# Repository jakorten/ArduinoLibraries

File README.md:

# ArduinoLibraries

This repo contains useful Arduino libraries for student and/or research projects.
| Code            | Description                                                                                                |   |
|-----------------|------------------------------------------------------------------------------------------------------------|---|
| [LEDTest](https://github.com/jakorten/SoftRoboticsDevBoard/tree/main/LEDTest)         | Sketch to test the normal LEDs of the DevBoard.                                                            |   |
| [Dual NeoPixel Test](https://github.com/jakorten/SoftRoboticsDevBoard/tree/main/NeoPixelTest) | Simple NeoPixel test for the two Neopixels. |   |
| [ActuatorTest](https://github.com/jakorten/SoftRoboticsDevBoard/tree/main/ActuatorTest)    | Sketch to test the four Actuators of the DevBoard.                                                         |   |
| [WireScanner](https://github.com/jakorten/SoftRoboticsDevBoard/tree/main/WireScanner)     | Sketch that allows to scan all i2c devices on different SERCOM wires of the DevBoard.                                                |   |
| [FRAM_MB85RC_I2C](https://github.com/jakorten/ArduinoLibraries/tree/main/FRAM_MB85RC_I2C) | Is a modified library based on the one from [@sosandroid](https://github.com/sosandroid/FRAM_MB85RC_I2C) that supports SERCOM for Arduino SAMD controllers. |   |

Disclaimer: the sketches and/or libraries might not have been written by myself (but of course I credit the original authors). Coding standards might not be up to the standard we teach and want you to follow. We will try to refactor these libraries as much as possible but often as we need them for rapid prototyping only that might not have been feasible.

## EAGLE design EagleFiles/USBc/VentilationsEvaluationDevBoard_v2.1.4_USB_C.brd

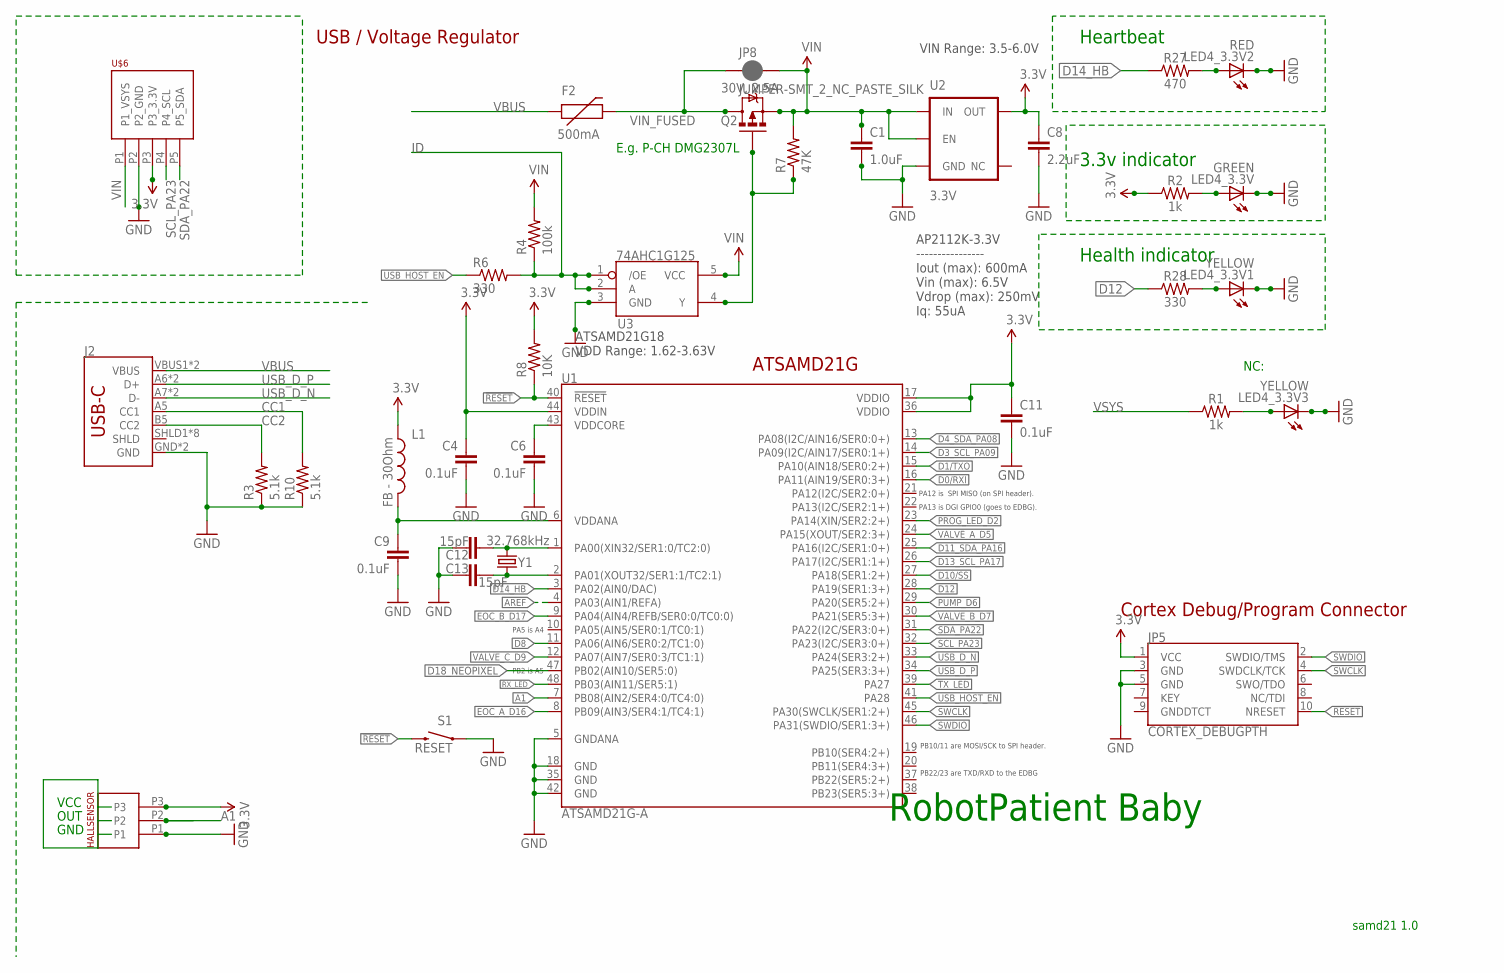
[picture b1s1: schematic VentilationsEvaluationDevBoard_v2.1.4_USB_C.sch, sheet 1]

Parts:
C1: 1.0uF; 0805
C4, C6, C9, C11: 0.1uF; 0402-CAP
C8: 2.2uF; 0603-CAP
C12, C13: 15pF; 0402-CAP
F2: 500mA; PTC-1206
HALLSENSOR: PHOENIX_PTSM_M3_TH_UP; PTSM_M3_THR_UP
J2: USB_C16PIN; USB-C-16P
JP5: CORTEX_DEBUGPTH; 2X5-PTH-1.27MM
JP8: JUMPER-SMT_2_NC_PASTE_SILK; SMT-JUMPER_2_NC_PASTE_SILK
L1: FB - 30Ohm; 0603
LED4_3.3V: GREEN; LED-0603
LED4_3.3V1, LED4_3.3V3: YELLOW; LED-0603
LED4_3.3V2: RED; LED-0603
Q2: 30V, 2.5A; SOT23-3
R1, R2: 1k; 0603
R3, R10: 5.1k; 0603-RES
R4: 100k; 0603-RES
R6: 330; 0603-RES
R7: 47K; 0603-RES
R8: 10K; 0603-RES
R27: 470; 0603
R28: 330; 0603
S1: RESET; TACTILE_SWITCH_SMD_4.6X2.8MM
U1: ATSAMD21G-A; TQFP-48
U2: 3.3V; SOT23-5
U3: 74AHC1G125; SOT23-5
U$6: PHOENIX_PTSM_M5_TH_UP; PTSM_M5_THR_UP
Y1: 32.768kHz; CRYSTAL-SMD-3.2X1.5MM

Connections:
3.3V: C4.1, C8.1, C11.1, HALLSENSOR.P3, JP5.1 (VCC), L1.1, R2.1, R8.2, U1.17 (VDDIO), U1.36 (VDDIO), U1.44 (VDDIN), U2.5 (OUT), U$6.P3 (P3_3.3V); also elsewhere on the board
!RESET: JP5.10 (NRESET), R8.1, S1.3 (2), S1.4 (2), U1.40 (!RESET!)
A1: HALLSENSOR.P2, U1.7 (PB08(AIN2/SER4:0/TC4:0))
AREF: U1.4 (PA03(AIN1/REFA))
CC1: J2.A5 (CC1), R10.2
CC2: J2.B5 (CC2), R3.2
D0/RXI: U1.16 (PA11(AIN19/SER0:3+))
D1/TXO: U1.15 (PA10(AIN18/SER0:2+))
D3_SCL_PA09: U1.14 (PA09(I2C/AIN17/SER0:1+)); also elsewhere on the board
D4_SDA_PA08: U1.13 (PA08(I2C/AIN16/SER0:0+)); also elsewhere on the board
D8: U1.11 (PA06(AIN6/SER0:2/TC1:0))
D10/SS: U1.27 (PA18(SER1:2+))
D11_SDA_PA16: U1.25 (PA16(I2C/SER1:0+)); also elsewhere on the board
D12: R28.1, U1.28 (PA19(SER1:3+))
D13_SCL_PA17: U1.26 (PA17(I2C/SER1:1+)); also elsewhere on the board
D14_HB: R27.1, U1.3 (PA02(AIN0/DAC))
D18_NEOPIXEL: U1.47 (PB02(AIN10/SER5:0)); also elsewhere on the board
EOC_A_D16: U1.8 (PB09(AIN3/SER4:1/TC4:1)); also elsewhere on the board
EOC_B_D17: U1.9 (PA04(AIN4/REFB/SER0:0/TC0:0)); also elsewhere on the board
GND: C1.2, C4.2, C6.2, C8.2, C9.2, C11.2, C12.1, C13.2, HALLSENSOR.P1, J2.GND, J2.GND2 (GND), JP5.3 (GND), JP5.5 (GND), LED4_3.3V.C, LED4_3.3V1.C, LED4_3.3V2.C, LED4_3.3V3.C, R3.1, R10.1, S1.1, S1.2 (1), U1.5 (GNDANA), U1.18 (GND), U1.35 (GND), U1.42 (GND), U2.2 (GND), U3.3 (GND), U$6.P2 (P2_GND); also elsewhere on the board
ID: R4.1, R6.2, U3.1 (/OE), U3.2 (A)
unnamed: LED4_3.3V2.A, R27.2
unnamed: LED4_3.3V1.A, R28.2
unnamed: LED4_3.3V3.A, R1.2
unnamed: C12.2, U1.1 (PA00(XIN32/SER1:0/TC2:0)), Y1.P$2 (2)
unnamed: Q2.1 (G), R7.1, U3.4 (Y)
unnamed: C13.1, U1.2 (PA01(XOUT32/SER1:1/TC2:1)), Y1.P$1 (1)
unnamed: LED4_3.3V.A, R2.2
PROG_LED_D2: U1.23 (PA14(XIN/SER2:2+)); also elsewhere on the board
PUMP_D6: U1.29 (PA20(SER5:2+)); also elsewhere on the board
RX_LED: U1.48 (PB03(AIN11/SER5:1))
SCL_PA23: U1.32 (PA23(I2C/SER3:0+)), U$6.P4 (P4_SCL); also elsewhere on the board
SDA_PA22: U1.31 (PA22(I2C/SER3:0+)), U$6.P5 (P5_SDA); also elsewhere on the board
SWCLK: JP5.4 (SWDCLK/TCK), U1.45 (PA30(SWCLK/SER1:2+))
SWDIO: JP5.2 (SWDIO/TMS), U1.46 (PA31(SWDIO/SER1:3+))
TX_LED: U1.39 (PA27)
USB_D_N: J2.A7 (D-), J2.B7 (D-), U1.33 (PA24(SER3:2+))
USB_D_P: J2.A6 (D+), J2.B6 (D+), U1.34 (PA25(SER3:3+))
USB_HOST_EN: R6.1, U1.41 (PA28)
VALVE_A_D5: U1.24 (PA15(XOUT/SER2:3+)); also elsewhere on the board
VALVE_B_D7: U1.30 (PA21(SER5:3+)); also elsewhere on the board
VALVE_C_D9: U1.12 (PA07(AIN7/SER0:3/TC1:1)); also elsewhere on the board
VBUS: F2.1, J2.VBUS1 (VBUS), J2.VBUS2 (VBUS)
VDDANA: C9.1, L1.2, U1.6 (VDDANA)
VDDCORE: C6.1, U1.43 (VDDCORE)
VIN: C1.1, JP8.2, Q2.2 (S), R4.2, R7.2, U2.1 (IN), U2.3 (EN), U3.5 (VCC), U$6.P1 (P1_VSYS); also elsewhere on the board
VIN_FUSED: F2.2, JP8.1, Q2.3 (D); also elsewhere on the board
VSYS: R1.1; also elsewhere on the board

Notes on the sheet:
3.3v indicator
samd21 1.0
RobotPatient Baby
Health indicator
Heartbeat
USB / Voltage Regulator
VIN Range: 3.5-6.0V
AP2112K-3.3V ---------------- Iout (max): 600mA Vin (max): 6.5V Vdrop (max): 250mV Iq: 55uA
PB22/23 are TXD/RXD to the EDBG
PB10/11 are MOSI/SCK to SPI header.
PA12 is SPI MISO (on SPI header).
PA13 is DGI GPIO0 (goes to EDBG).
PA5 is A4
PB2 is A5
ATSAMD21G
ATSAMD21G18 VDD Range: 1.62-3.63V
Cortex Debug/Program Connector
NC:
VCC
OUT
GND
E.g. P-CH DMG2307L

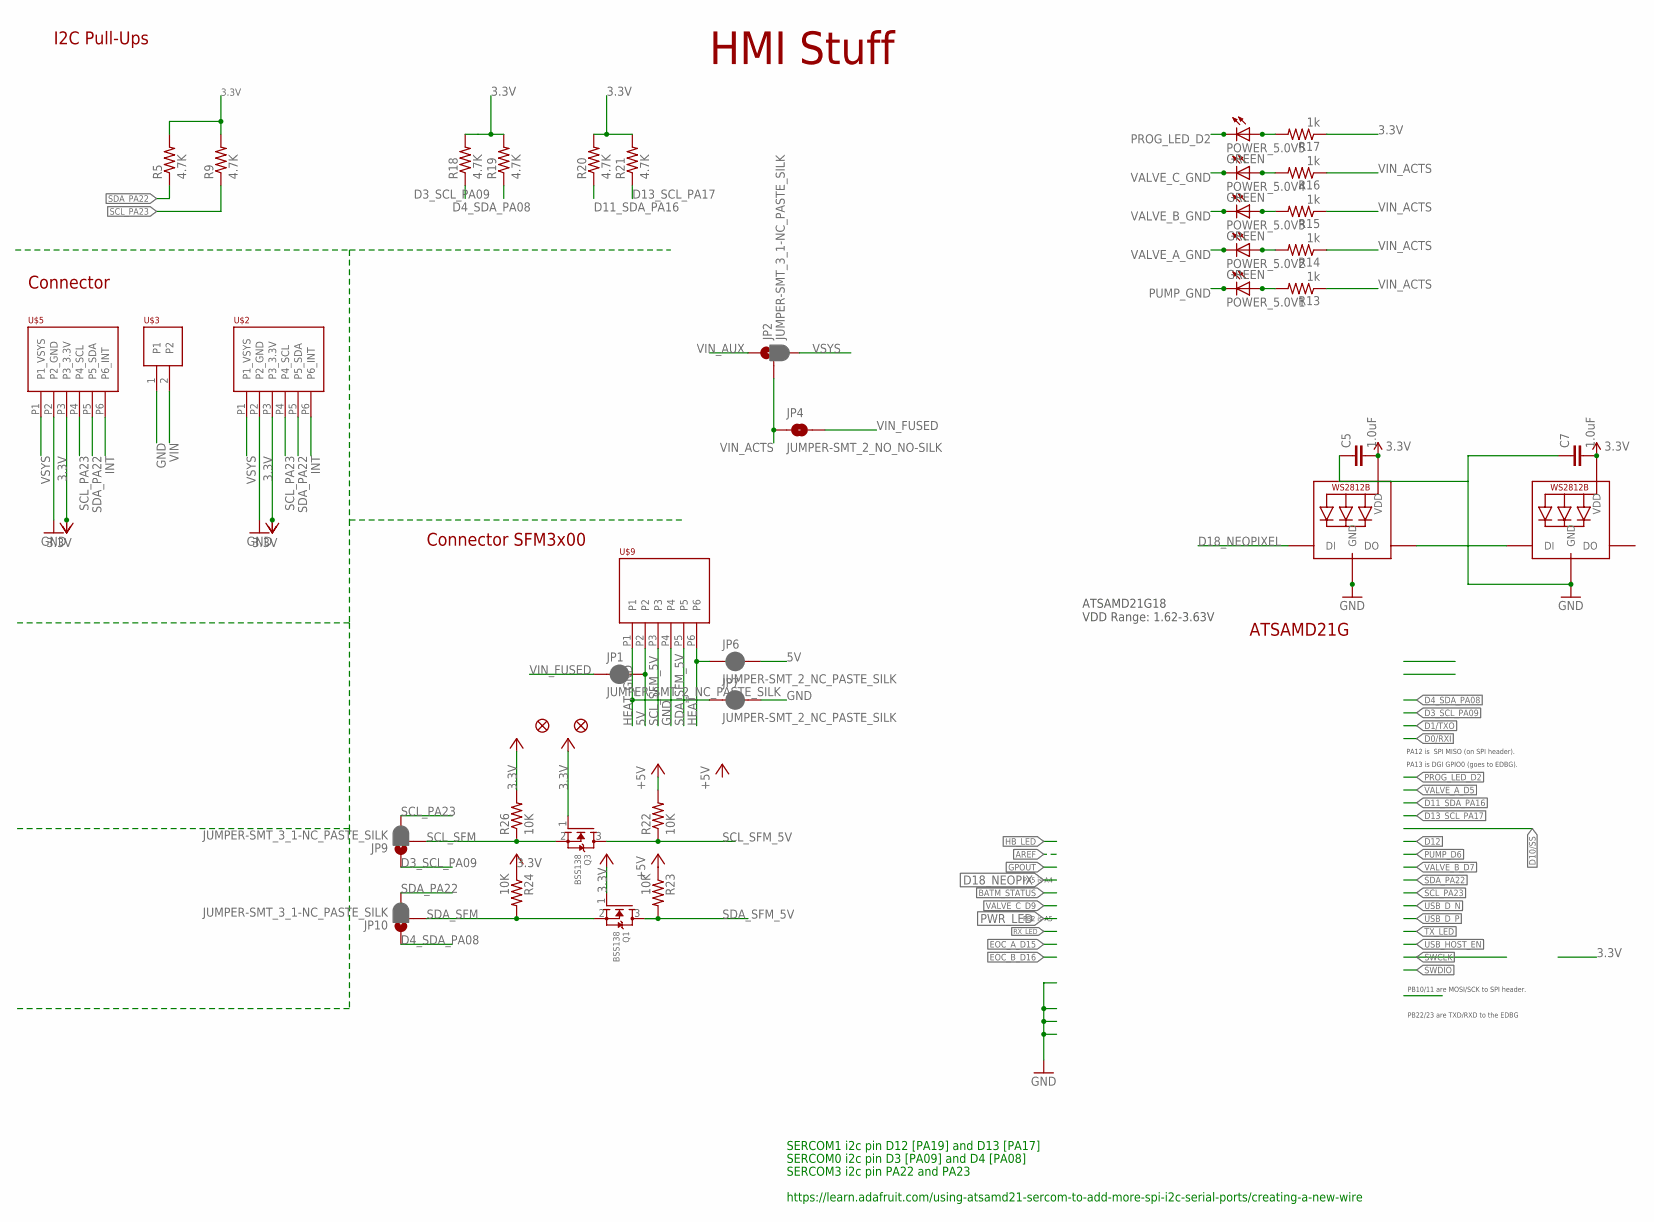
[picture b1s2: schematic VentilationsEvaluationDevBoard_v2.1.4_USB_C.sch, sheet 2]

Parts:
C5, C7: 1.0uF; 0805
FD1, FD2: FIDUCIAL1X2; FIDUCIAL-1X2
JP1, JP6, JP7: JUMPER-SMT_2_NC_PASTE_SILK; SMT-JUMPER_2_NC_PASTE_SILK
JP2, JP9, JP10: JUMPER-SMT_3_1-NC_PASTE_SILK; SMT-JUMPER_3_1-NC_PASTE_SILK
JP4: JUMPER-SMT_2_NO_NO-SILK; SMT-JUMPER_2_NO_NO-SILK
LED1, LED2: WS2812B3535; LED3535
POWER_5.0V1, POWER_5.0V2, POWER_5.0V3, POWER_5.0V4, POWER_5.0V5: GREEN; LED-0603
Q1, Q3: BSS138; SOT23
R5, R9, R18, R19, R20, R21: 4.7K; 0603-RES@1
R13, R14, R15, R16, R17: 1k; 0603-RES
R22, R23, R24, R26: 10K; R0805
U$2, U$5: PHOENIX_PTSM_M6_TH_I2CPPANGLE; PTSM_M6_THRHOLE
U$3: PHOENIX_PTSM_M2_TH; PTSM_M2_THRHOLE
U$9: PHOENIX_PTSM_M6_TH_UP_NEUTRAL; PTSM_M6_TH_UP_NEUTRAL

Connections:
3.3V: C5.2, C7.2, LED1.2 (VDD), LED2.2 (VDD), Q1.1 (G), Q3.1 (G), R5.2, R9.2, R17.1, R18.2, R19.2, R20.2, R21.2, R24.1, R26.2, U$2.P3 (P3_3.3V), U$5.P3 (P3_3.3V); also elsewhere on the board
5V: JP1.2, JP6.2, R22.2, R23.1, U$9.P2
D3_SCL_PA09: JP9.1, R18.1; also elsewhere on the board
D4_SDA_PA08: JP10.1, R19.1; also elsewhere on the board
D11_SDA_PA16: R20.1; also elsewhere on the board
D13_SCL_PA17: R21.1; also elsewhere on the board
D18_NEOPIXEL: LED1.1 (DI); also elsewhere on the board
GND: C5.1, C7.1, JP7.2, LED1.4 (GND), LED2.4 (GND), U$2.P2 (P2_GND), U$3.1, U$5.P2 (P2_GND), U$9.P4; also elsewhere on the board
HEAT: JP6.1, U$9.P6
HEAT_GND: JP7.1, U$9.P1
INT: U$2.P6 (P6_INT), U$5.P6 (P6_INT)
unnamed: POWER_5.0V1.A, R13.2
unnamed: POWER_5.0V2.A, R14.2
unnamed: POWER_5.0V3.A, R15.2
unnamed: POWER_5.0V4.A, R16.2
unnamed: POWER_5.0V5.A, R17.2
NEOPIXEL_2: LED1.3 (DO), LED2.1 (DI)
PROG_LED_D2: POWER_5.0V5.C; also elsewhere on the board
PUMP_GND: POWER_5.0V1.C; also elsewhere on the board
SCL_PA23: JP9.3, R9.1, U$2.P4 (P4_SCL), U$5.P4 (P4_SCL); also elsewhere on the board
SCL_SFM: JP9.2, Q3.2 (S), R26.1
SCL_SFM_5V: Q3.3 (D), R22.1, U$9.P3
SDA_PA22: JP10.3, R5.1, U$2.P5 (P5_SDA), U$5.P5 (P5_SDA); also elsewhere on the board
SDA_SFM: JP10.2, Q1.2 (S), R24.2
SDA_SFM_5V: Q1.3 (D), R23.2, U$9.P5
VALVE_A_GND: POWER_5.0V2.C; also elsewhere on the board
VALVE_B_GND: POWER_5.0V3.C; also elsewhere on the board
VALVE_C_GND: POWER_5.0V4.C; also elsewhere on the board
VIN: U$3.2; also elsewhere on the board
VIN_ACTS: JP2.2, JP4.1, R13.1, R14.1, R15.1, R16.1; also elsewhere on the board
VIN_AUX: JP2.1
VIN_FUSED: JP1.1, JP4.2; also elsewhere on the board
VSYS: JP2.3, U$2.P1 (P1_VSYS), U$5.P1 (P1_VSYS); also elsewhere on the board

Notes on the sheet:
PB22/23 are TXD/RXD to the EDBG
PB10/11 are MOSI/SCK to SPI header.
PA12 is SPI MISO (on SPI header).
PA13 is DGI GPIO0 (goes to EDBG).
PA5 is A4
PB2 is A5
ATSAMD21G
ATSAMD21G18 VDD Range: 1.62-3.63V
I2C Pull-Ups
HMI Stuff
SERCOM1 i2c pin D12 [PA19] and D13 [PA17]
https://learn.adafruit.com/using-atsamd21-sercom-to-add-more-spi-i2c-serial-ports/creating-a-new-wire
SERCOM0 i2c pin D3 [PA09] and D4 [PA08]
SERCOM3 i2c pin PA22 and PA23
Connector SFM3x00
Connector

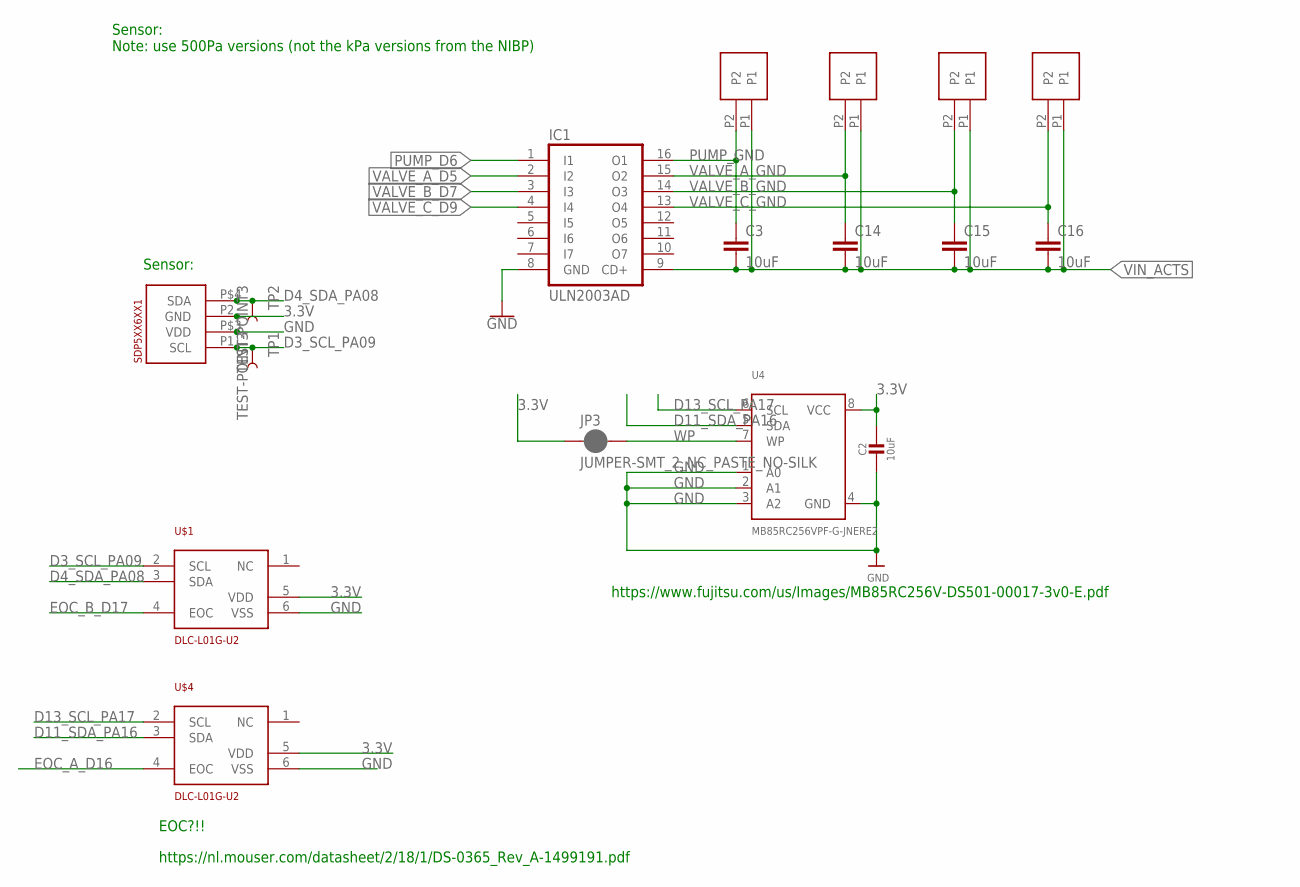
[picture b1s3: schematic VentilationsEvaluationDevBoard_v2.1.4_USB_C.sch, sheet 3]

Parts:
C2: 10uF; _0805MP
C3, C14, C15, C16: 10uF; 0805
IC1: ULN2003AD; SO16
JP3: JUMPER-SMT_2_NC_PASTE_NO-SILK; SMT-JUMPER_2_NC_PASTE_NO-SILK
PUMP: PHOENIX_PTSM_M2_SMD; PTSM_M2_SMD
SDP5XX6XX1: SDP5XX_6XX
TP1, TP2: TEST-POINT3; PAD.03X.03
U4: MB85RC256VPF-G-JNERE2; SOIC8_208MIL
U$1, U$4: DLC-L01G-U2
VALVE_A: PHOENIX_PTSM_M2_SMD; PTSM_M2_SMD
VALVE_B: PHOENIX_PTSM_M2_SMD; PTSM_M2_SMD
VALVE_C: PHOENIX_PTSM_M2_SMD; PTSM_M2_SMD

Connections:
3.3V: C2.1, JP3.1, SDP5XX6XX1.P2 (GND), U4.8 (VCC), U$1.5 (VDD), U$4.5 (VDD); also elsewhere on the board
D3_SCL_PA09: SDP5XX6XX1.P1 (SCL), TP1.P$1, U$1.2 (SCL); also elsewhere on the board
D4_SDA_PA08: SDP5XX6XX1.P$4 (SDA), TP2.P$1, U$1.3 (SDA); also elsewhere on the board
D11_SDA_PA16: U4.5 (SDA), U$4.3 (SDA); also elsewhere on the board
D13_SCL_PA17: U4.6 (SCL), U$4.2 (SCL); also elsewhere on the board
EOC_A_D16: U$4.4 (EOC); also elsewhere on the board
EOC_B_D17: U$1.4 (EOC); also elsewhere on the board
GND: C2.2, IC1.8 (GND), SDP5XX6XX1.P$3 (VDD), U4.1 (A0), U4.2 (A1), U4.3 (A2), U4.4 (GND), U$1.6 (VSS), U$4.6 (VSS); also elsewhere on the board
PUMP_D6: IC1.1 (I1); also elsewhere on the board
PUMP_GND: C3.1, IC1.16 (O1), PUMP.P2; also elsewhere on the board
VALVE_A_D5: IC1.2 (I2); also elsewhere on the board
VALVE_A_GND: C14.1, IC1.15 (O2), VALVE_A.P2; also elsewhere on the board
VALVE_B_D7: IC1.3 (I3); also elsewhere on the board
VALVE_B_GND: C15.1, IC1.14 (O3), VALVE_B.P2; also elsewhere on the board
VALVE_C_D9: IC1.4 (I4); also elsewhere on the board
VALVE_C_GND: C16.1, IC1.13 (O4), VALVE_C.P2; also elsewhere on the board
VIN_ACTS: C3.2, C14.2, C15.2, C16.2, IC1.9 (CD+), PUMP.P1, VALVE_A.P1, VALVE_B.P1, VALVE_C.P1; also elsewhere on the board
WP: JP3.2, U4.7 (WP)

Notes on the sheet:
Sensor: Note: use 500Pa versions (not the kPa versions from the NIBP)
Sensor:
EOC?!!
https://nl.mouser.com/datasheet/2/18/1/DS-0365_Rev_A-1499191.pdf
https://www.fujitsu.com/us/Images/MB85RC256V-DS501-00017-3v0-E.pdf

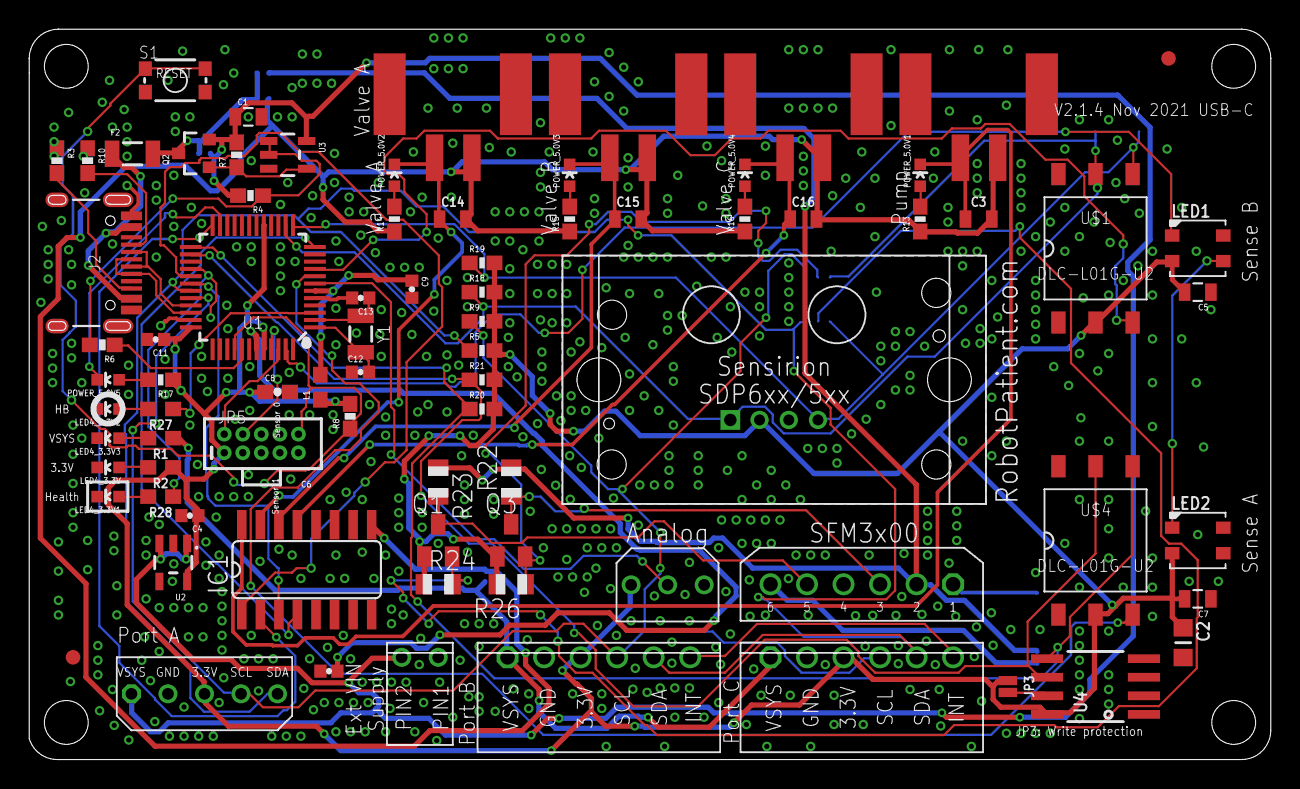
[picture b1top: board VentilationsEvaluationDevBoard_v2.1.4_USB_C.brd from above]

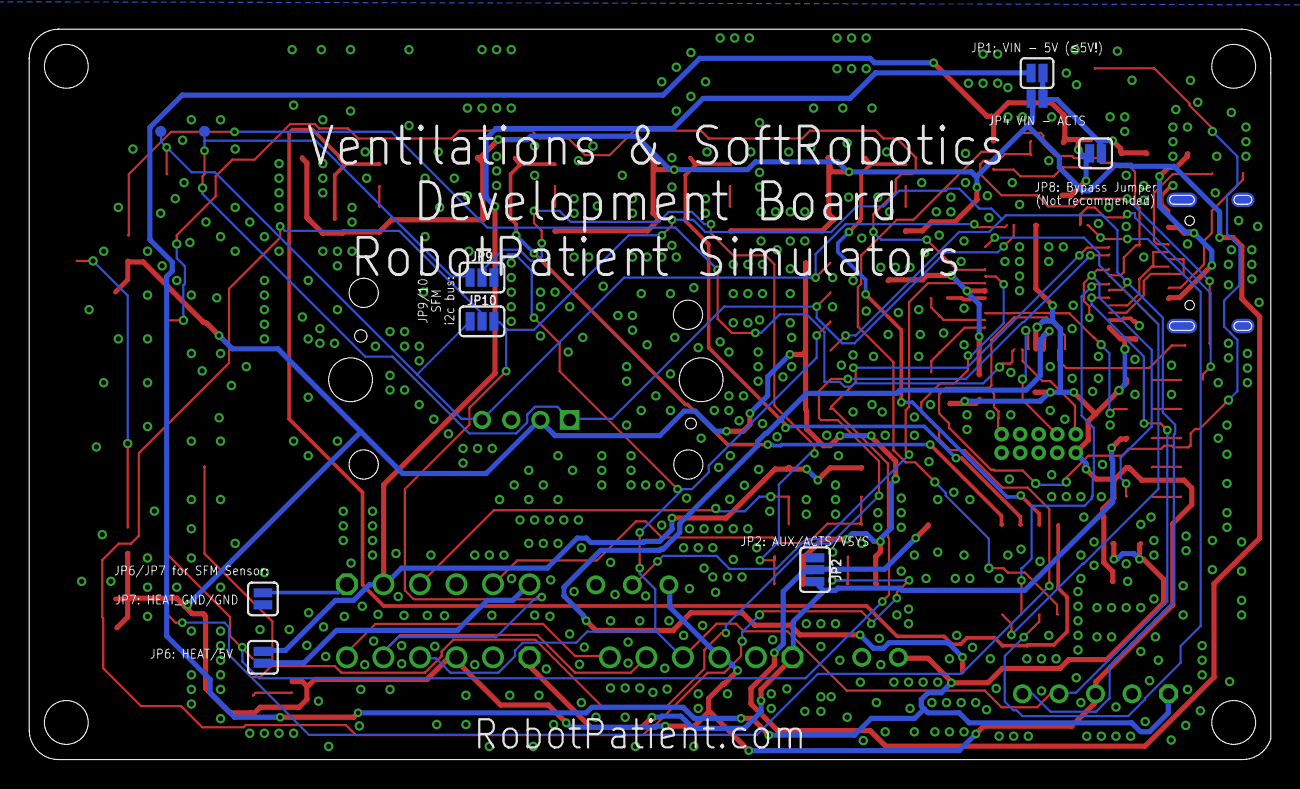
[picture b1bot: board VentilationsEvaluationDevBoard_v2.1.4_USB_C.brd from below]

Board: 2 copper layers, 85.0 x 50.0 mm, 91 parts (10 on the bottom side), 61 nets.

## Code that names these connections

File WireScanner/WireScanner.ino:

// --------------------------------------
// i2c_scanner for SAMDxx microcontrollers with Arduino bootloader 
// (e.g. Feather M0 Express by Adafruit)
//
// This sketch tests the standard 7-bit addresses
// Devices with higher bit address might not be seen properly.
//
// Changes for RobotPatient Simulators and HAN University of Applied Sciences
// Nov 5, 2021 J.A. Korten
// Scanner for 3 i2c channels:
// Escpecially for DevBoard for Ventilations / Soft Robotics actuators.
//
// Based on earlier work by Krodal and Nick Gammon
// See also: https://learn.adafruit.com/using-atsamd21-sercom-to-add-more-spi-i2c-serial-ports/creating-a-new-wire
//
// This sketch tests the standard 7-bit addresses
// Devices with higher bit address might not be seen properly.
//
//
// Changes for RobotPatient Simulators and HAN University of Applied Sciences
// Nov 5, 2021 J.A. Korten
// Scanner for 3 i2c channels:
// Escpecially for DevBoard for Ventilations / Soft Robotics actuators.
//

#include <Wire.h> // SERCOM3?
#include "wiring_private.h" // pinPeripheral() function

// i2c system bus
#define W0_SCL 21 // PA22 D20 / SDA SERCOM3.0 SERCOM5.0
#define W0_SDA 20 // PA23 D21 / SCL SERCOM3.1 SERCOM5.1

#define W1_SCL 3 // PA09  D3    SERCOM0.1 SERCOM2.1
#define W1_SDA 4 // PA08  D4    SERCOM0.0 SERCOM2.0

#define W2_SCL 13 // PA17 D13   SERCOM1.1 SERCOM3.1
#define W2_SDA 11 // PA16 D11   SERCOM1.0 SERCOM3.0

// SDA will be on SERCOM1.0 D11 and SCL will be on SERCOM1.1 D13

// Default Wire:
// I2C / SERCOM 0:
// PA22 / SDA on pin 11;
// PA23 / SCL on pin 12;

// On the Development Board:
// D13_SCL_PA17 /﻿D11_SDA_PA16
// D3_SCL_PA09 / D4_SDA_PA08
// SCL_PA23 / SDA_PA22 are they mixed up? Needs checking Nov 5, 2021. SFM Could be switched using jumper wires on the pads JP9/JP10

TwoWire Wire0(&sercom3, W0_SDA, W0_SCL); // Right sensor
TwoWire Wire1(&sercom2, W1_SDA, W1_SCL); // Left sensor, diff sensor
TwoWire Wire2(&sercom1, W2_SDA, W2_SCL); // EEPROM / SRAM
// And of course standard Wire

void setup()
{
  Serial.begin(115200);
  delay(1500);
  Wire.begin();
  Wire0.begin();
  Wire1.begin();
  Wire2.begin();

  // Assign pins 4 & 3 to SERCOM functionality
  pinPeripheral(W1_SDA, PIO_SERCOM_ALT);
  pinPeripheral(W1_SCL, PIO_SERCOM_ALT);

  // Assign pins 13 & 11 to SERCOM functionality
  pinPeripheral(W2_SDA, PIO_SERCOM);
  pinPeripheral(W2_SCL, PIO_SERCOM);
  delay(1500);

  Serial.println("Ready...");
  delay(1500);
}


void loop()
{
  //exit;
  digitalWrite(12, HIGH);
  reportDevicesOn(&Wire0, "0: on SERCOM3 (D20d/D21c)");
  reportDevicesOn(&Wire1, "1: on SERCOM2 (D4_SDA_PA08 / ﻿D3_SCL_PA09)");
  reportDevicesOn(&Wire2, "2: on SERCOM1 (D11_PA16_SDA1 /﻿D13_PA17_SCL1)");

  delay(2500);           // wait 5 seconds for next scan
}

void reportDevicesOn(TwoWire *wire, String label) {
  byte error, address;
  int nDevices;
  Serial.print("Scanning bus 1: ");
  Serial.println(label);
  for (address = 1; address < 127; address++ )
  {
    digitalWrite(12, LOW);
    // The i2c_scanner uses the return value of
    // the Write.endTransmisstion to see if
    // a device did acknowledge to the address.
    wire->beginTransmission(address);
    error = wire->endTransmission();

    if (error == 0)
    {
      digitalWrite(12, HIGH);
      Serial.print("I2C device found at address 0x");
      if (address < 16)
        Serial.print("0");
      Serial.print(address, HEX);
      Serial.println("  !");
      printDeviceName(address);

      nDevices++;
    }
    else if (error == 4)
    {
      Serial.print("Unknow error at address 0x");
      if (address < 16)
        Serial.print("0");
      Serial.println(address, HEX);
    }
  }
  if (nDevices == 0)
    Serial.println("No I2C devices found on bus 1\n");
  else
    Serial.println("done\n");
}

void printDeviceName(int address) {
  // Print recognized i2c device names:
  if (address == 0x25) {
    Serial.println("Sensirion SDP800-500Pa found...");
  }
  if (address == 0x26) {
    Serial.println("Sensirion SDP800-501Pa found...");
  }
  if (address == 0x29) {
    Serial.println("DLC-L01G-U2 found...");
  }
  if (address == 0x40) {
    Serial.println("Sensirion SDP610-500Pa found...");
  }
  if (address == 0x50) {
    Serial.println("FRAM/EEPROM found...");
  }
  if (address == 0x51) {
    Serial.println("More memory found? Could be 1M FRAM.");
  }
  if (address == 0x7C) {
    Serial.println("RESERVED...");
  }
}

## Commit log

2021-11-05 Changes for SERCOM
2021-11-05 WireScanner for DevBoard
2021-11-05 LED test for Heartbeat and Health
2021-11-05 Actuator test sketch
2021-11-05 Update to folders
2021-11-05 Added gerber files for DevBoard
2021-11-05 Added eagle files for DevBoard
2021-11-05 NeoPixels Test Sketch
2021-11-06 New library for AllSensors DLC
2021-11-22 USB-C changed to 2.1.4

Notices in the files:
parts and their libraries:
SparkFun-Capacitors: Licensing: CC v3.0 Share-Alike You are welcome to use this library for commercial purposes.
SparkFun-Resistors: Licensing: Creative Commons ShareAlike 4.0 International - https://creativecommons.org/licenses/by-sa/4.0
